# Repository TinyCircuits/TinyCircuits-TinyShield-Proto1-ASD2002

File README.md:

# TinyCircuits TinyShield Proto1 Board
# ASD2002 Rev4

These are the design files for the TinyCircuits ASD2002 Rev 4 PCB.  This is a Tiny shield board (Square Version, 20mm x 20mm, or Circular 20mm diameter) that has all of the shield signals brought out to 2mm spaced holes. 

Format is in Cadsoft Eagle format - Eagle version 6.2 was used for the original design.

For more infomation on this, check out the product page at Tiny-Circuits.com:  https://tiny-circuits.com/tiny-shield-proto-board-1.html

#License:

Design by TinyCircuits.
All design files are released under the Creative Commons Attribution Share-Alike 3.0 License, see the following link for details: http://creativecommons.org/licenses/by-sa/3.0

All text above must be included in any redistribution or derived design

This project uses designs and concepts developed as part of the Arduino project and the LilyPad project.  The TinyCircuits design files themselves (schematics, PCB and libraries) are not directly derived from these works' design files and have been created new, however the concepts and basic architecture behind the TinyDuino and TinyLily products are derived and we thank the hard work of the organizations below for their contributions to open-source hardware:
  
Original Arduino Uno Design by Team Arduino

LilyPad Arduino Design by Leah Buechley and Sparkfun Electronics

Please support the open-source hardware community

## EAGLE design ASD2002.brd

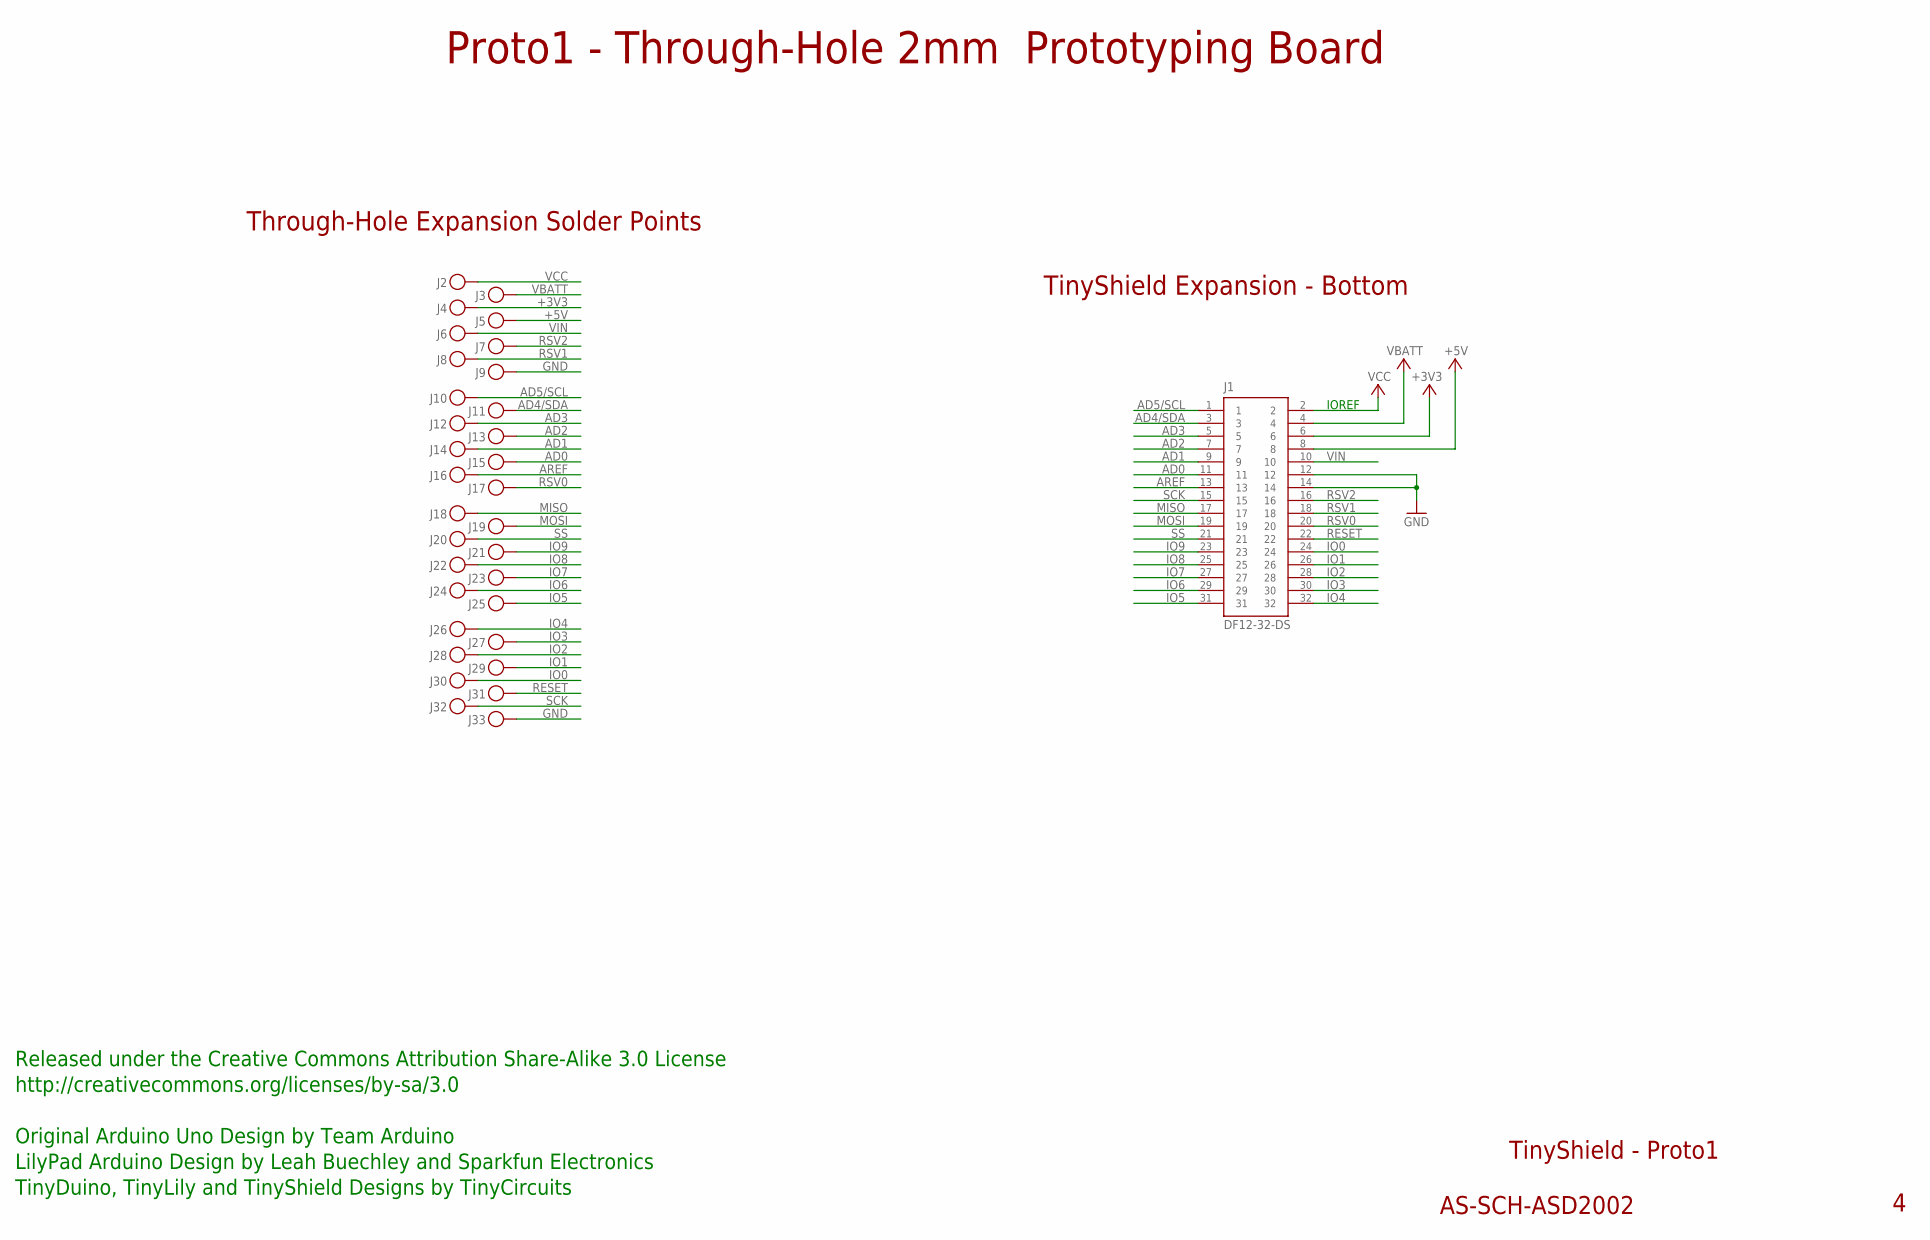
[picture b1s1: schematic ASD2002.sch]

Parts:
J1: DF12-32-DS; PARTNO AS-ITM-00012
J2, J3, J4, J5, J6, J7, J8, J9, J10, J11, J12, J13, J14, J15, J16, J17, J18, J19, J20, J21, J22, J23, J24, J25, J26, J27, J28, J29, J30, J31, J32, J33: PIN_1X.1"; 1X.1"; PARTNO COPPER

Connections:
+3V3: J1.6, J4.1
+5V: J1.8, J5.1
AD0: J1.11, J15.1
AD1: J1.9, J14.1
AD2: J1.7, J13.1
AD3: J1.5, J12.1
AD4/SDA: J1.3, J11.1
AD5/SCL: J1.1, J10.1
AREF: J1.13, J16.1
GND: J1.12, J1.14, J9.1, J33.1
IO0: J1.24, J30.1
IO1: J1.26, J29.1
IO2: J1.28, J28.1
IO3: J1.30, J27.1
IO4: J1.32, J26.1
IO5: J1.31, J25.1
IO6: J1.29, J24.1
IO7: J1.27, J23.1
IO8: J1.25, J22.1
IO9: J1.23, J21.1
MISO: J1.17, J18.1
MOSI: J1.19, J19.1
RESET: J1.22, J31.1
RSV0: J1.20, J17.1
RSV1: J1.18, J8.1
RSV2: J1.16, J7.1
SCK: J1.15, J32.1
SS: J1.21, J20.1
VBATT: J1.4, J3.1
VCC: J1.2, J2.1
VIN: J1.10, J6.1

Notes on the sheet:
TinyShield Expansion - Bottom
TinyShield - Proto1
AS-SCH-ASD2002
IOREF
Released under the Creative Commons Attribution Share-Alike 3.0 License
http://creativecommons.org/licenses/by-sa/3.0
LilyPad Arduino Design by Leah Buechley and Sparkfun Electronics
TinyDuino, TinyLily and TinyShield Designs by TinyCircuits
Through-Hole Expansion Solder Points
Original Arduino Uno Design by Team Arduino
Proto1 - Through-Hole 2mm Prototyping Board

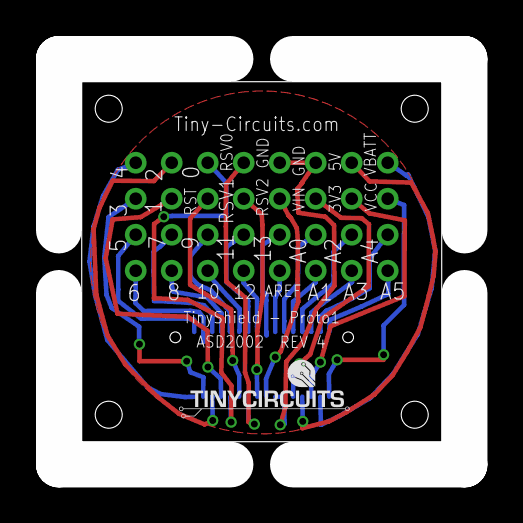
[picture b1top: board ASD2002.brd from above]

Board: 2 copper layers, 20.0 x 20.0 mm, 34 parts (1 on the bottom side), 31 nets.

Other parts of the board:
U$1: DOCFIELD-TINYCIRCUITS-PCB

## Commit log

2013-06-30 Updated project link
2013-12-24 Updated to Rev4
2014-08-24 Updated Link
